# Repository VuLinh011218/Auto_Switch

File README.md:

# Auto Switch – Hệ thống giám sát và điều khiển thiết bị phòng

**STM32F103C8T6 | DHT22 · LDR · PIR | ILI9341 + XPT2046 | 4 relay**

[Thiết kế KiCad](Hardware/01_Design) · [Schematic PDF](Hardware/02_Schematic_PDF/Smart_Switch.pdf) · [BOM](Hardware/03_Bom) · [Gerber](Hardware/04_Gerber) · [Firmware – branch ILI9341](https://github.com/VuLinh011218/Auto_Switch/tree/ILI9341/Firmware)

## 1. Giới thiệu

Auto Switch là mạch giám sát các điều kiện trong phòng và điều khiển **quạt, hai đèn và máy hút ẩm**. STM32F103C8T6 đọc dữ liệu từ cảm biến nhiệt độ – độ ẩm, ánh sáng và chuyển động; trạng thái hệ thống được đưa lên màn hình TFT 2.8 inch. Người dùng thao tác bằng cảm ứng hoặc nút nhấn vật lý.

Hệ thống được thiết kế với hai chế độ:

- **Manual:** Người dùng bật/tắt từng thiết bị.
- **Auto:** Vi điều khiển điều khiển thiết bị theo dữ liệu cảm biến và ngưỡng đã đặt.

## 2. Chức năng

| Chức năng | Mô tả theo thiết kế |
| --- | --- |
| Đo môi trường | DHT22 đo nhiệt độ, độ ẩm; LDR đo mức sáng; PIR AM312 phát hiện chuyển động |
| Hiển thị | TFT ILI9341 hiển thị thông số môi trường, chế độ và trạng thái bốn thiết bị |
| Điều khiển bằng tay | Bật/tắt tải bằng màn hình cảm ứng XPT2046 hoặc nút nhấn |
| Điều khiển tự động | Quạt theo nhiệt độ, máy hút ẩm theo độ ẩm, hai đèn theo ánh sáng và chuyển động |
| Đầu ra | Bốn relay điều khiển quạt, đèn 1, đèn 2 và máy hút ẩm |

### Auto Mode

- **Quạt và máy hút ẩm:** đóng/ngắt theo các ngưỡng nhiệt độ, độ ẩm tương ứng.
- **Đèn 1 và đèn 2:** kết hợp tín hiệu PIR với hai ngưỡng ánh sáng riêng biệt. Khi trời tối hơn, đèn 2 được bật thêm; khi sáng trở lại, đèn 2 tắt trước đèn 1.
- **Thời gian giữ đèn:** mỗi lần PIR phát hiện chuyển động, bộ đếm 5 phút bắt đầu lại. Nếu không có chuyển động mới, hai đèn tắt khi hết thời gian.

## 3. Sơ đồ hệ thống

**Hình 1. Sơ đồ khối chức năng**

```mermaid
flowchart LR
    S["DHT22 / LDR / PIR"] --> MCU["STM32F103C8T6"]
    B["4 nút nhấn"] --> MCU
    T["XPT2046 Touch"] <-->|SPI2| MCU
    MCU -->|SPI1| LCD["TFT ILI9341"]
    MCU -->|GPIO| D["PC817 + transistor"]
    D --> R["4 relay 12 VDC"]
    R --> L["Quạt / Đèn 1 / Đèn 2 / Máy hút ẩm"]
```

**Figure 2. Power Distribution**

```mermaid
flowchart LR
    IN["12 V DC Adapter"] --> F["Fuse / Input Protection"]
    F --> V12["12 V Rail"]
    V12 --> RELAY["Four 12 V Relay Coils"]
    V12 --> BUCK["TPS54231 Buck Converter"]
    BUCK --> V33["3.3 V Rail"]
    V33 --> MCU["STM32F103C8T6"]
    V33 --> LCD["ILI9341 Display + XPT2046 Touch"]
    V33 --> SENS["DHT22 / LDR / PIR Sensors"]
```

## 4. Phần cứng

| Thành phần | Chức năng |
| --- | --- |
| STM32F103C8T6 | Vi điều khiển ARM Cortex-M3, xử lý cảm biến và lệnh điều khiển |
| DHT22 (AM2302) | Đo nhiệt độ và độ ẩm |
| LDR + LM393 | Đọc mức ánh sáng qua ngõ ra analog AO |
| PIR AM312 | Phát hiện chuyển động |
| ILI9341 2.8 inch | Màn hình TFT 240 × 320, giao tiếp SPI |
| XPT2046 | Bộ điều khiển cảm ứng, giao tiếp SPI |
| HF46F 12-HS1 (4 chiếc) | Relay điều khiển bốn tải |
| PC817 + transistor | Tầng điều khiển relay |
| TPS54231DR | Hạ áp 12 V xuống 3.3 V |
| 4 nút nhấn | Điều khiển trực tiếp tại thiết bị |

## 5. Firmware

(https://github.com/VuLinh011218/Auto_Switch/tree/ILI9341/Firmware).

```text
Firmware/
├── app/                 # Chọn chế độ, xử lý lệnh và ngưỡng điều khiển
├── middleware/
│   ├── input_mgr/       # Xử lý nút nhấn và cảm ứng
│   └── ui/              # Giao diện TFT
├── device/
│   ├── button/          # Nút nhấn, debounce
│   ├── ili9341/         # Driver màn hình
│   ├── relay/           # Điều khiển 4 relay
│   ├── sensor/          # Giao diện đọc cảm biến
│   └── xpt2046/         # Driver cảm ứng
├── Core/                # Khởi tạo MCU và ngoại vi
├── Drivers/             # STM32 HAL / CMSIS
└── Smart_Room_Control.ioc
```

## 6. Cấu trúc repository

```text
Auto_Switch/
├── Hardware/
│   ├── 01_Design/            # Project KiCad 10, schematic và PCB
│   ├── 02_Schematic_PDF/     # Bản PDF sơ đồ nguyên lý
│   ├── 03_Bom/               # Danh sách linh kiện
│   └── 04_Gerber/            # Gerber và drill files
├── Firmware/                 # Mã nguồn nằm trên branch ILI9341
└── .gitignore
```

## 7. Tài liệu dự án

- [Sơ đồ nguyên lý (PDF)](Hardware/02_Schematic_PDF/Smart_Switch.pdf)
- [Project KiCad](Hardware/01_Design/Smart_Switch.kicad_pro)
- [Thiết kế PCB](Hardware/01_Design/Smart_Switch.kicad_pcb)
- [Danh sách linh kiện (BOM)](Hardware/03_Bom/Smart_Switch.csv)
- [File Gerber](Hardware/04_Gerber)

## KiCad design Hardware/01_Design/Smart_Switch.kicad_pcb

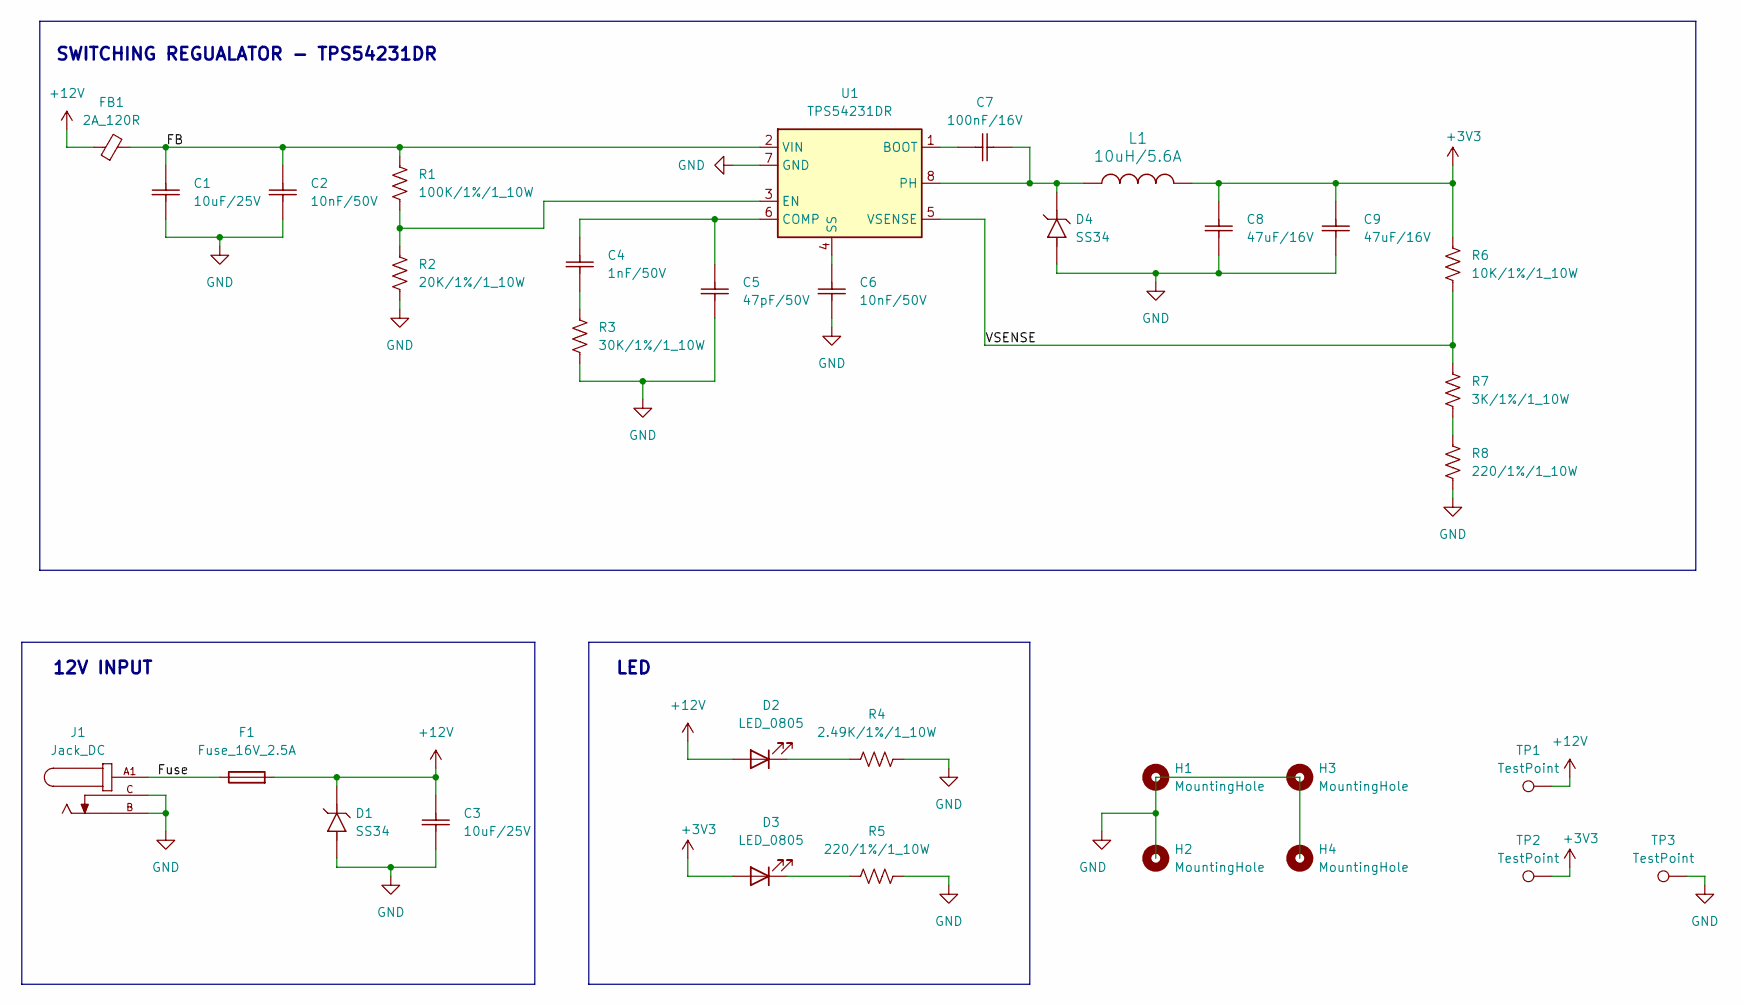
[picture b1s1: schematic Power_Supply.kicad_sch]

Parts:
C1, C3: 10uF/25V; Ceramic_Cap_0603
C2, C6: 10nF/50V; Ceramic_Cap_0603
C4: 1nF/50V; Ceramic_Cap_0603
C5: 47pF/50V; Ceramic_Cap_0603
C7: 100nF/16V; Ceramic_Cap_0603
C8, C9: 47uF/16V; Ceramic_Cap_1206
D1, D4: SS34; D_SMA
D2, D3: LED_0805
F1: Fuse_16V_2.5A; Fuse_1812_4532Metric
FB1: 2A_120R; FB_0805
H1, H2, H3, H4: MountingHole; MountingHole_3.2mm_M3_DIN965_Pad_TopBottom
J1: Jack_DC; Jack-DC
L1: 10uH/5.6A; IND_CD75NP_SUM
R1: 100K/1%/1_10W; Res_0603
R2: 20K/1%/1_10W; Res_0603
R3: 30K/1%/1_10W; Res_0603
R4: 2.49K/1%/1_10W; Res_0603
R5, R8: 220/1%/1_10W; Res_0603
R6: 10K/1%/1_10W; Res_0603
R7: 3K/1%/1_10W; Res_0603
TP1, TP2, TP3: TestPoint; TestPoint_Pad_2.0x2.0mm
U1: TPS54231DR; SOIC-8

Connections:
+3V3: C8.2, C9.2, D3.2 (A), L1.1, R6.2, TP2.1 (1_1); also elsewhere on the board
+12V: C3.2, D1.2 (K), D2.2 (A), F1.2, FB1.1, TP1.1 (1_1); also elsewhere on the board
/Power_Supply/FB: C1.2, C2.2, FB1.2, R1.2, U1.2 (VIN)
/Power_Supply/Fuse: F1.1, J1.A1, J1.A2
/Power_Supply/VSENSE: R6.1, R7.2, U1.5 (VSENSE)
GND: C1.1, C2.1, C3.1, C5.1, C6.1, C8.1, C9.1, D1.1 (A), D4.1 (A), J1.B, J1.C, R2.1, R3.1, R4.2, R5.2, R8.1, TP3.1 (1_1), U1.7 (GND); also elsewhere on the board
unnamed: C4.1, R3.2
unnamed: D2.1 (K), R4.1
unnamed: D3.1 (K), R5.1
unnamed: C7.1, D4.2 (K), L1.2, U1.8 (PH)
unnamed: R7.1, R8.2
unnamed: C7.2, U1.1 (BOOT)
unnamed: C4.2, C5.2, U1.6 (COMP)
unnamed: R1.1, R2.2, U1.3 (EN)
unnamed: C6.2, U1.4 (SS)

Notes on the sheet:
LED
SWITCHING REGUALATOR - TPS54231DR
12V INPUT

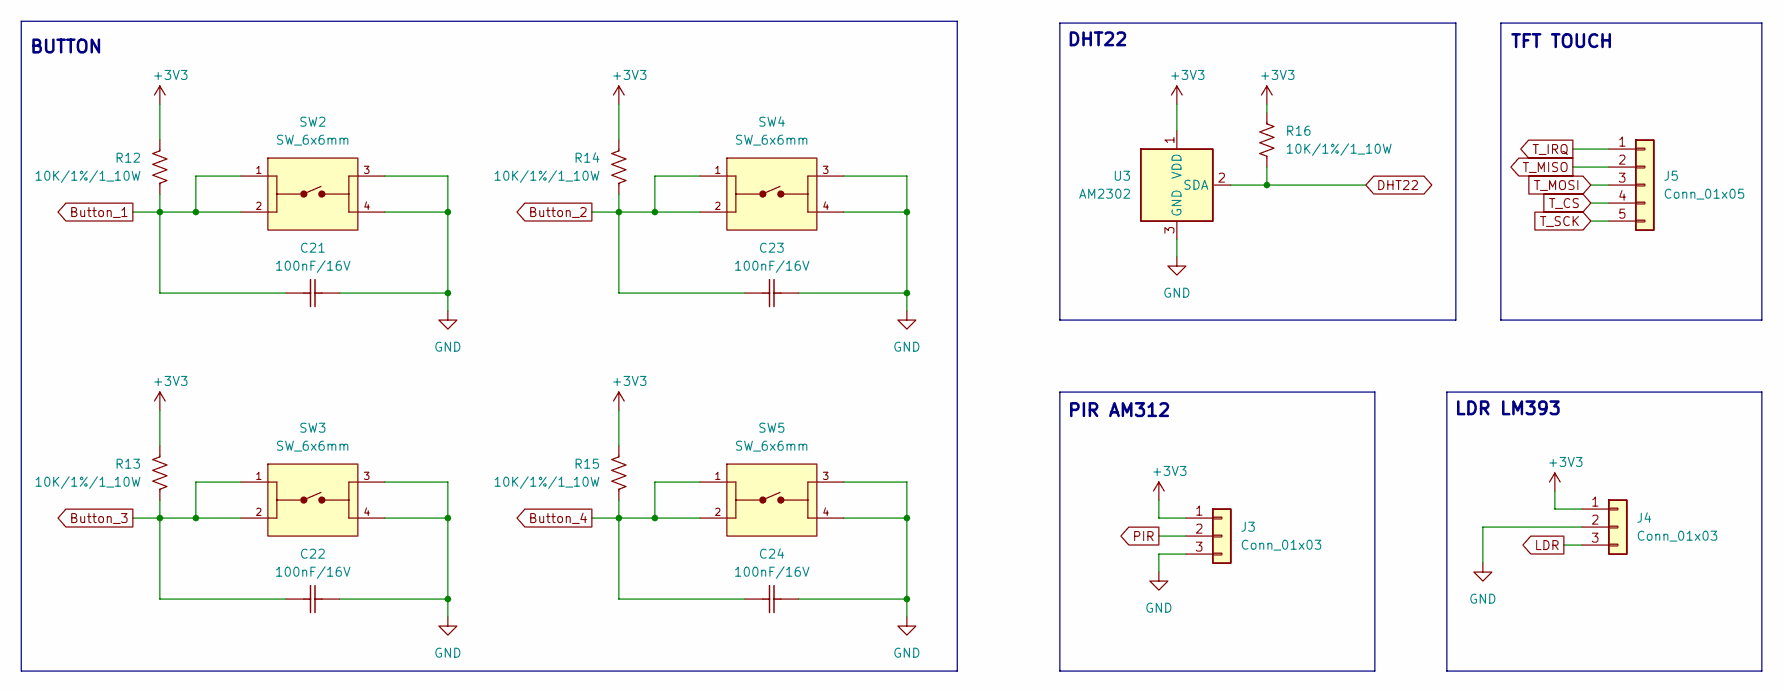
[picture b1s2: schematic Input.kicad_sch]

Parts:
C21, C22, C23, C24: 100nF/16V; Ceramic_Cap_0603
J3, J4: Conn_01x03; PinHeader_1x03_P2.54mm_Vertical
J5: Conn_01x05; PinHeader_1x05_P2.54mm_Vertical
R12, R13, R14, R15, R16: 10K/1%/1_10W; Res_0603
SW2, SW3, SW4, SW5: SW_6x6mm; TE_FSM4JSMA
U3: AM2302; ASAIR_AM2302_P2.54mm_Vertical

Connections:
+3V3: J3.1, J4.1, R12.1, R13.1, R14.1, R15.1, R16.2, U3.1 (VDD); also elsewhere on the board
Button_1: C21.1, R12.2, SW2.1, SW2.2; also elsewhere on the board
Button_2: C23.1, R14.2, SW4.1, SW4.2; also elsewhere on the board
Button_3: C22.1, R13.2, SW3.1, SW3.2; also elsewhere on the board
Button_4: C24.1, R15.2, SW5.1, SW5.2; also elsewhere on the board
DHT22: R16.1, U3.2 (SDA); also elsewhere on the board
GND: C21.2, C22.2, C23.2, C24.2, J3.3, J4.2, SW2.3, SW2.4, SW3.3, SW3.4, SW4.3, SW4.4, SW5.3, SW5.4, U3.3 (GND), U3.4 (GND); also elsewhere on the board
LDR: J4.3; also elsewhere on the board
PIR: J3.2; also elsewhere on the board
T_CS: J5.4; also elsewhere on the board
T_IRQ: J5.1; also elsewhere on the board
T_MISO: J5.2; also elsewhere on the board
T_MOSI: J5.3; also elsewhere on the board
T_SCK: J5.5; also elsewhere on the board

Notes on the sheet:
LDR LM393
BUTTON
TFT TOUCH
DHT22
PIR AM312

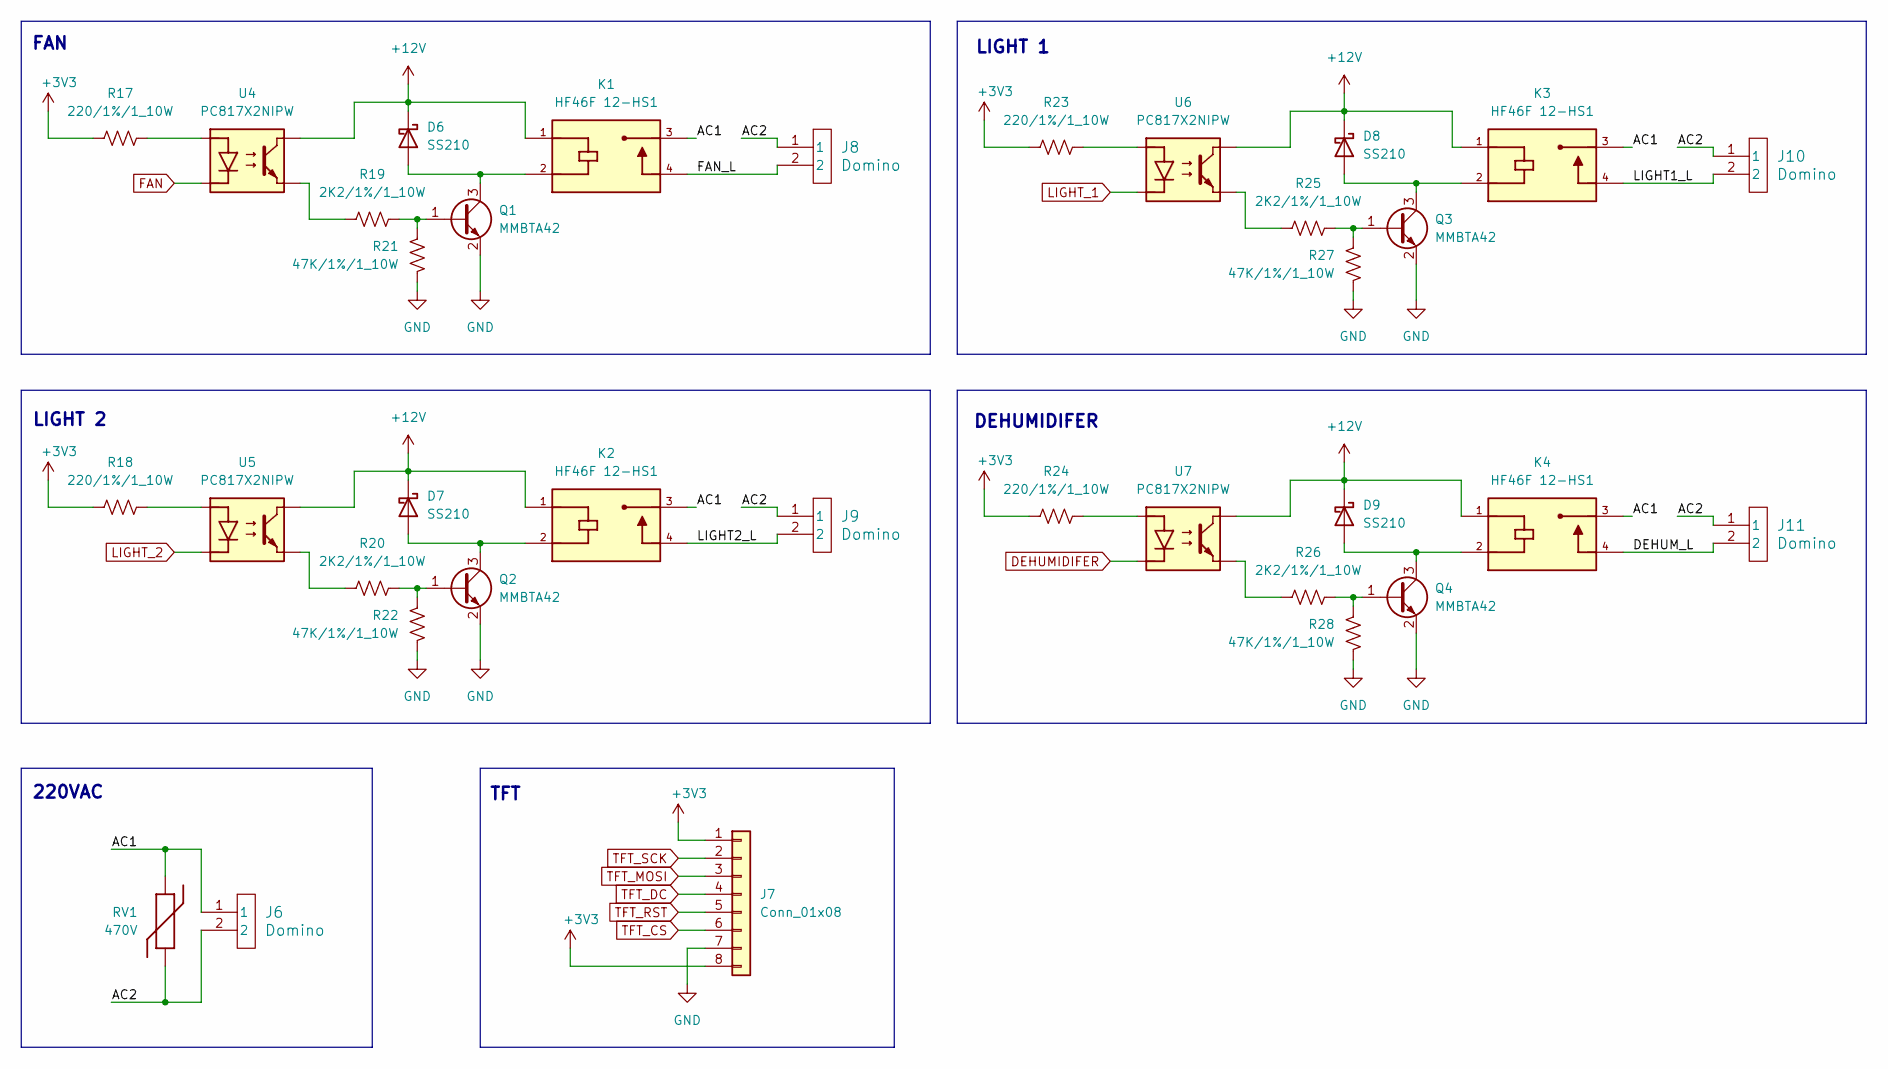
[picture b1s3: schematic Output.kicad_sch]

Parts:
D6, D7, D8, D9: SS210; D_SMA
J6, J8, J9, J10, J11: Domino; Domino_2P
J7: Conn_01x08; PinHeader_1x08_P2.54mm_Vertical
K1, K2, K3, K4: HF46F 12-HS1; RELAY_HF46F_005-HS1
Q1, Q2, Q3, Q4: MMBTA42; SOT-23
R17, R18, R23, R24: 220/1%/1_10W; Res_0603
R19, R20, R25, R26: 2K2/1%/1_10W; Res_0603
R21, R22, R27, R28: 47K/1%/1_10W; Res_0603
RV1: 470V; RV_Disc_D7mm_W3.4mm_P5mm
U4, U5, U6, U7: PC817X2NIPW

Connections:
+3V3: J7.1, J7.8, R17.1, R18.1, R23.1, R24.1; also elsewhere on the board
+12V: D6.1 (K), D7.1 (K), D8.1 (K), D9.1 (K), K1.1, K2.1, K3.1, K4.1, U4.4 (C), U5.4 (C), U6.4 (C), U7.4 (C); also elsewhere on the board
/Output/AC1: J6.1, K1.3, K2.3, K3.3, K4.3, RV1.2
/Output/AC2: J6.2, J8.1, J9.1, J10.1, J11.1, RV1.1
/Output/DEHUM_L: J11.2, K4.4
/Output/FAN_L: J8.2, K1.4
/Output/LIGHT1_L: J10.2, K3.4
/Output/LIGHT2_L: J9.2, K2.4
DEHUMIDIFER: U7.2 (K); also elsewhere on the board
FAN: U4.2 (K); also elsewhere on the board
GND: J7.7, Q1.2 (E), Q2.2 (E), Q3.2 (E), Q4.2 (E), R21.1, R22.1, R27.1, R28.1; also elsewhere on the board
LIGHT_1: U6.2 (K); also elsewhere on the board
LIGHT_2: U5.2 (K); also elsewhere on the board
unnamed: D6.2 (A), K1.2, Q1.3 (C)
unnamed: D7.2 (A), K2.2, Q2.3 (C)
unnamed: D8.2 (A), K3.2, Q3.3 (C)
unnamed: D9.2 (A), K4.2, Q4.3 (C)
unnamed: Q1.1 (B), R19.2, R21.2
unnamed: Q2.1 (B), R20.2, R22.2
unnamed: Q3.1 (B), R25.2, R27.2
unnamed: Q4.1 (B), R26.2, R28.2
unnamed: R17.2, U4.1 (A)
unnamed: R19.1, U4.3 (E)
unnamed: R18.2, U5.1 (A)
unnamed: R20.1, U5.3 (E)
unnamed: R23.2, U6.1 (A)
unnamed: R25.1, U6.3 (E)
unnamed: R24.2, U7.1 (A)
unnamed: R26.1, U7.3 (E)
TFT_CS: J7.6; also elsewhere on the board
TFT_DC: J7.4; also elsewhere on the board
TFT_MOSI: J7.3; also elsewhere on the board
TFT_RST: J7.5; also elsewhere on the board
TFT_SCK: J7.2; also elsewhere on the board

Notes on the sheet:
LIGHT 2
220VAC
LIGHT 1
FAN
TFT
DEHUMIDIFER

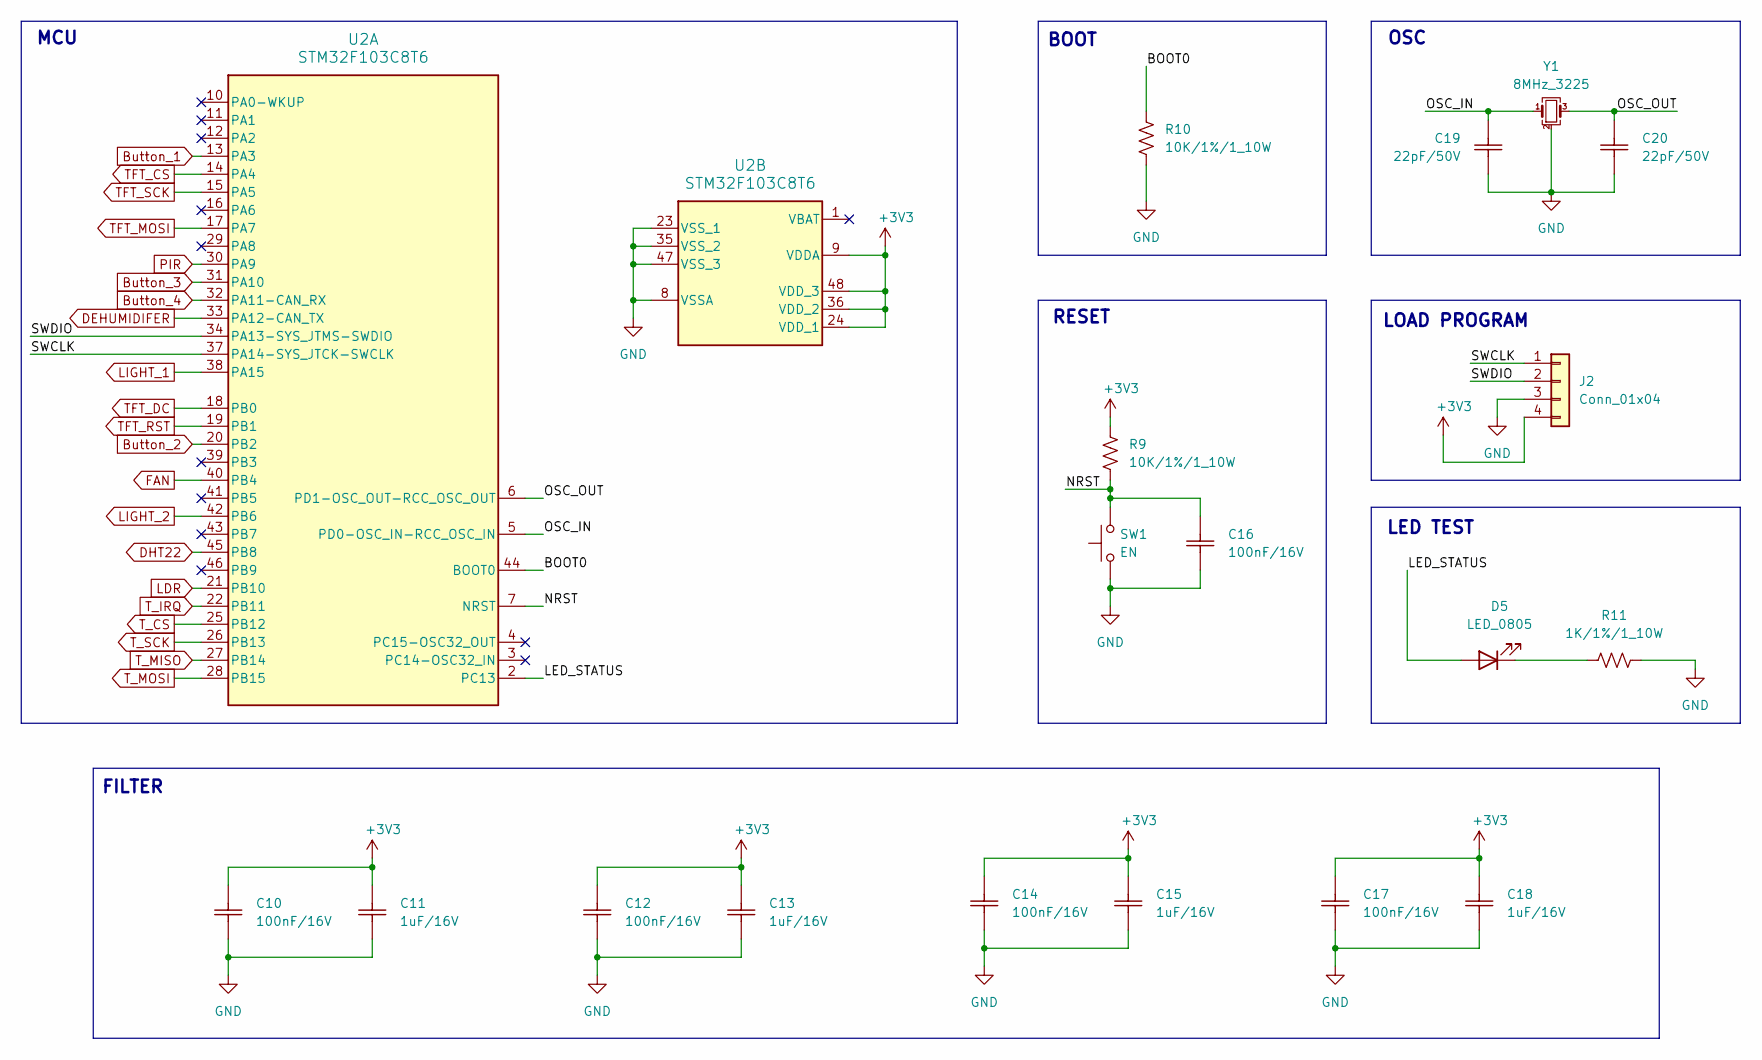
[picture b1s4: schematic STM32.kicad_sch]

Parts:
C10, C12, C14, C16, C17: 100nF/16V; Ceramic_Cap_0603
C11, C13, C15, C18: 1uF/16V; Ceramic_Cap_0603
C19, C20: 22pF/50V; Ceramic_Cap_0603
D5: LED_0805
J2: Conn_01x04; PinHeader_1x04_P2.54mm_Vertical
R9, R10: 10K/1%/1_10W; Res_0603
R11: 1K/1%/1_10W; Res_0603
SW1: EN; SW_SMD
U2: STM32F103C8T6; QFP50P900X900X160-48N
Y1: 8MHz_3225; Crystal_SMD_4PIN_3225

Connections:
+3V3: C10.2, C11.2, C12.2, C13.2, C14.2, C15.2, C17.2, C18.2, J2.4, R9.2, U2.9 (VDDA), U2.24 (VDD_1), U2.36 (VDD_2), U2.48 (VDD_3); also elsewhere on the board
/STM32/BOOT0: R10.2, U2.44 (BOOT0)
/STM32/LED_STATUS: D5.2 (A), U2.2 (PC13)
/STM32/NRST: C16.2, R9.1, SW1.2, U2.7 (NRST)
/STM32/OSC_IN: C19.2, U2.5 (PD0-OSC_IN-RCC_OSC_IN), Y1.1
/STM32/OSC_OUT: C20.2, U2.6 (PD1-OSC_OUT-RCC_OSC_OUT), Y1.3
/STM32/SWCLK: J2.1, U2.37 (PA14-SYS_JTCK-SWCLK)
/STM32/SWDIO: J2.2, U2.34 (PA13-SYS_JTMS-SWDIO)
Button_1: U2.13 (PA3); also elsewhere on the board
Button_2: U2.20 (PB2); also elsewhere on the board
Button_3: U2.31 (PA10); also elsewhere on the board
Button_4: U2.32 (PA11-CAN_RX); also elsewhere on the board
DEHUMIDIFER: U2.33 (PA12-CAN_TX); also elsewhere on the board
DHT22: U2.45 (PB8); also elsewhere on the board
FAN: U2.40 (PB4); also elsewhere on the board
GND: C10.1, C11.1, C12.1, C13.1, C14.1, C15.1, C16.1, C17.1, C18.1, C19.1, C20.1, J2.3, R10.1, R11.1, SW1.1, U2.8 (VSSA), U2.23 (VSS_1), U2.35 (VSS_2), U2.47 (VSS_3), Y1.2 (G), Y1.4 (G); also elsewhere on the board
LDR: U2.21 (PB10); also elsewhere on the board
LIGHT_1: U2.38 (PA15); also elsewhere on the board
LIGHT_2: U2.42 (PB6); also elsewhere on the board
unnamed: D5.1 (K), R11.2
PIR: U2.30 (PA9); also elsewhere on the board
TFT_CS: U2.14 (PA4); also elsewhere on the board
TFT_DC: U2.18 (PB0); also elsewhere on the board
TFT_MOSI: U2.17 (PA7); also elsewhere on the board
TFT_RST: U2.19 (PB1); also elsewhere on the board
TFT_SCK: U2.15 (PA5); also elsewhere on the board
T_CS: U2.25 (PB12); also elsewhere on the board
T_IRQ: U2.22 (PB11); also elsewhere on the board
T_MISO: U2.27 (PB14); also elsewhere on the board
T_MOSI: U2.28 (PB15); also elsewhere on the board
T_SCK: U2.26 (PB13); also elsewhere on the board

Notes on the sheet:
MCU
RESET
BOOT
OSC
FILTER
LOAD PROGRAM
LED TEST

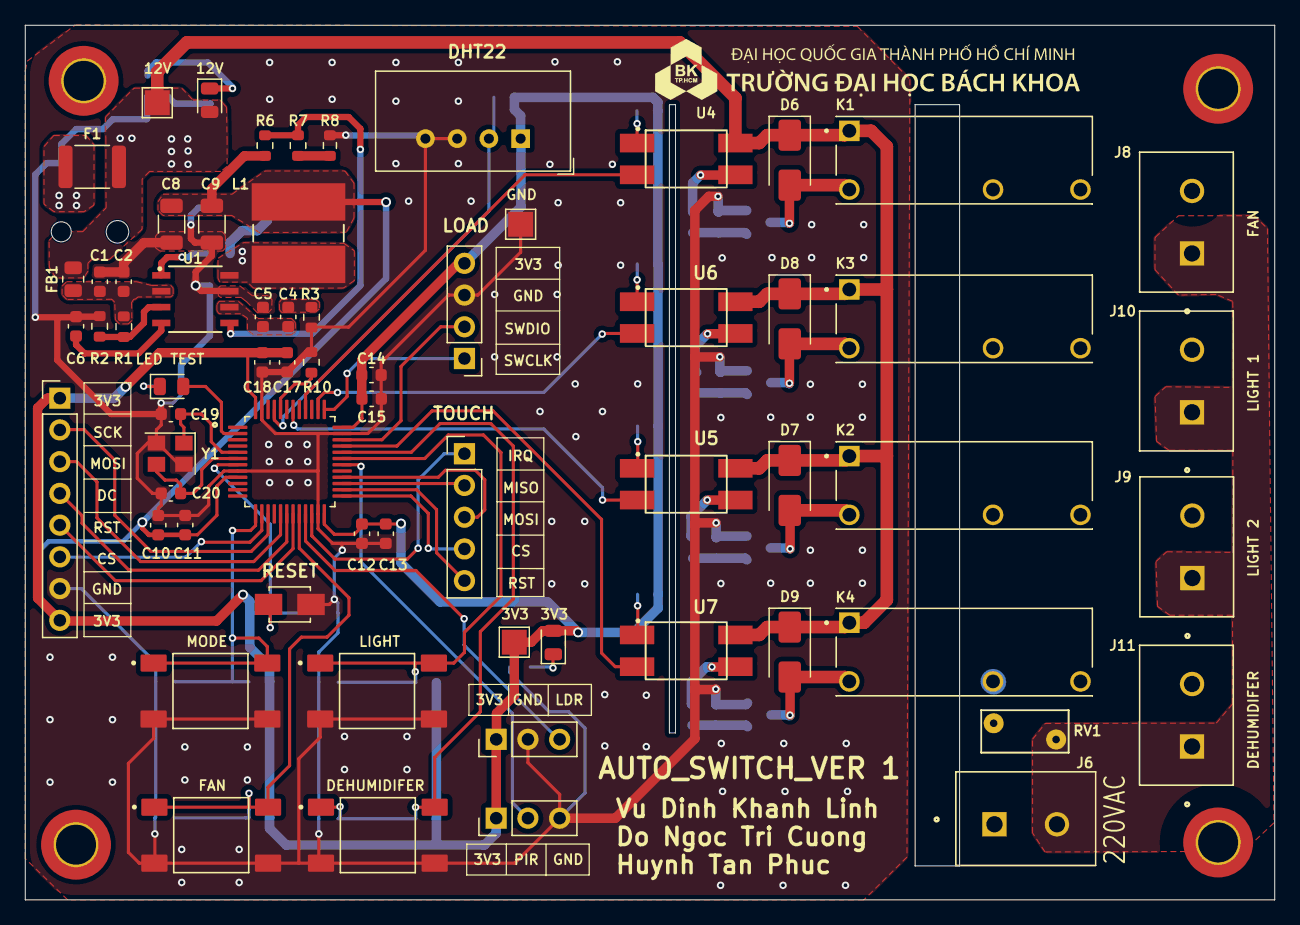
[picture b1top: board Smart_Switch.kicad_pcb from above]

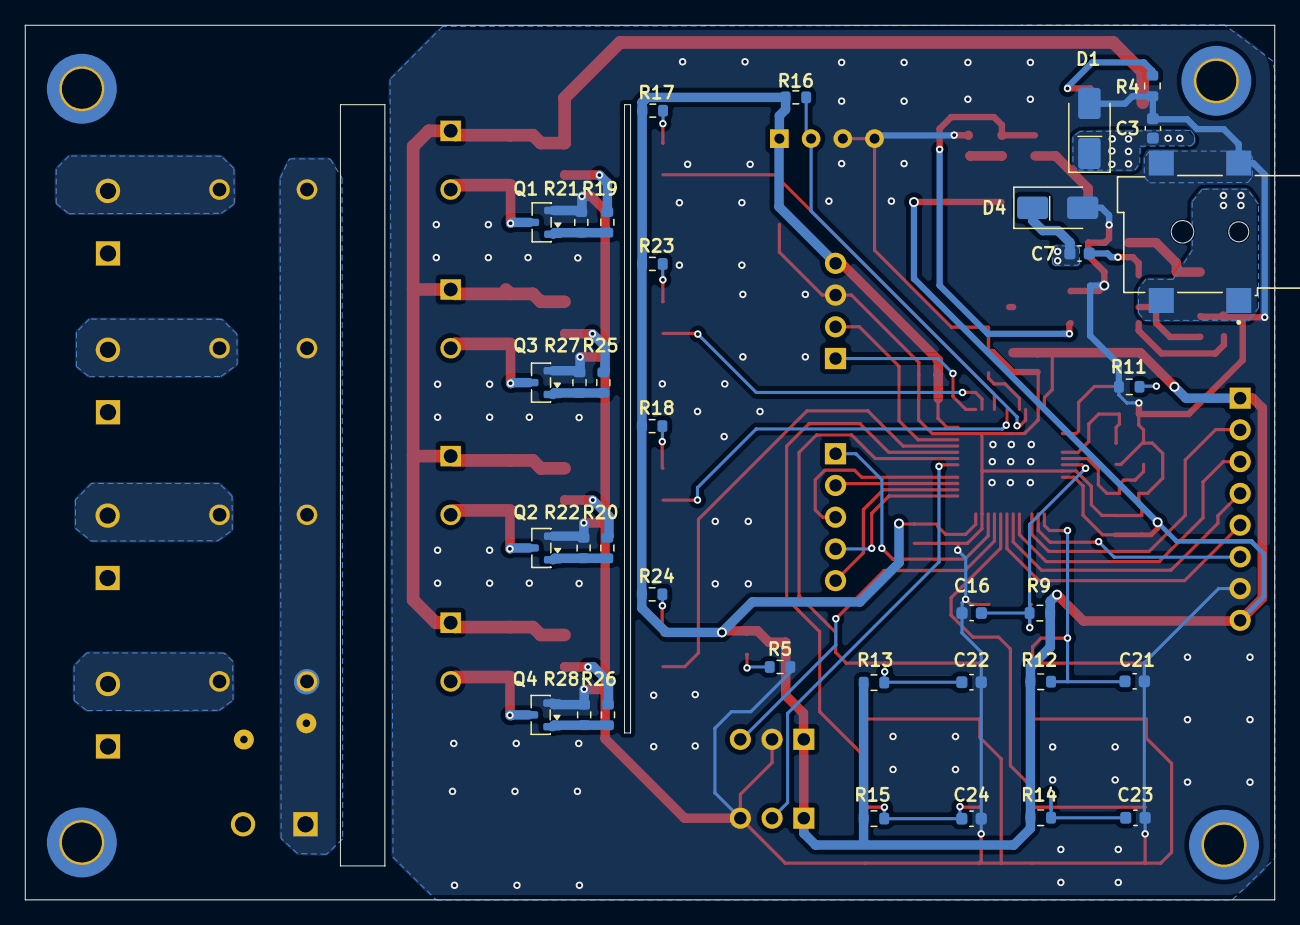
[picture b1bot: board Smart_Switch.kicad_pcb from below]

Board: 2 copper layers, 100.0 x 70.0 mm, 104 parts (35 on the bottom side), 66 nets.

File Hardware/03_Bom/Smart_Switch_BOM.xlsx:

Reference | Qty | Value | Supply part number | Supply name | Supply URL
C1,C3 | 2 | 10uF/25V | Tụ Gốm 0603 10uF 25V | Thegioiic | https://www.thegioiic.com/tu-gom-0603-10uf-25v
C2,C6 | 2 | 10nF/50V | Tụ Gốm 0603 10nF 50V | Thegioiic | https://www.thegioiic.com/tu-gom-0603-10nf-50v
C4 | 1 | 1nF/50V | Tụ Gốm 0603 1nF 50V | Thegioiic | https://www.thegioiic.com/tu-gom-0603-1nf-50v
C5 | 1 | 47pF/50V | Tụ Gốm 0603 47pF 50V | Thegioiic | https://www.thegioiic.com/tu-gom-0603-47pf-50v
C7,C10,C12,C14,C16,C17,C21,C22,C23,C24 | 10 | 100nF/16V | Tụ Gốm 0603 100nF (0.1uF) 16V | Thegioiic | https://www.thegioiic.com/tu-gom-0603-100nf-0-1uf-16v
C8,C9 | 2 | 47uF/16V | Tụ Gốm 1206 47uF 16V | Thegioiic | https://www.thegioiic.com/tu-gom-1206-47uf-16v
C11,C13,C15,C18 | 4 | 1uF/16V | Tụ Gốm 0603 1uF 16V | Thegioiic | https://www.thegioiic.com/tu-gom-0603-1uf-16v
C19,C20 | 2 | 22pF/50V | Tụ Gốm 0603 22pF 50V | Thegioiic | https://www.thegioiic.com/tu-gom-0603-22pf-50v
D1,D4 | 2 | SS34 | SS34 SMA Diode Shotky 3A 40V | Thegioiic | https://www.thegioiic.com/ss34-smc-diode-schottky-3a
D2,D3,D5 | 3 | LED_0805 | LED Xanh Lá 0805 Dán SMD Trong Suốt | Thegioiic | https://www.thegioiic.com/led-xanh-la-0805-dan-smd-trong-suot
D6,D7,D8,D9 | 4 | SS210 | SS210 SMA Diode Schottky 2A 100V | Thegioiic | https://www.thegioiic.com/ss210-sma-diode-schottky-2a-100v
F1 | 1 | Fuse_16V_2.5A | MF-MSMF250/16 Cầu Chì Tự Phục Hồi 1812 16V 2.5A | Thegioiic | https://www.thegioiic.com/mf-msmf250-16-cau-chi-tu-phuc-hoi-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
FB1 | 1 | 2A_120R | CBW201209U121T | Thegioiic | https://www.thegioiic.com/cbw201209u121t-ferrite-beads-2a-12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
J1 | 1 | Jack_DC | DC050 Đầu Nối Nguồn DC Cái 5521 Dán SMD Kim 2.1mm | Thegioiic | https://www.thegioiic.com/dc050-dau-noi-nguon-dc-cai-5521-da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
J2 | 1 | Conn_01x04 | Hàng Rào Đực Đơn 2.54mm 40 Chân 1 Hàng Cao 11.2mm Xuyên Lỗ Mạ Vàng | Thegioiic | https://www.thegioiic.com/hang-rao-duc-don-2-54mm-40-chan-1-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
J3,J4 | 2 | Conn_01x03 | Hàng Rào Cái Đơn 2.54mm 3 Chân 1 Hàng Cao 11.8mm Xuyên Lỗ | Thegioiic | https://www.thegioiic.com/hang-rao-cai-don-2-54mm-3-chan-1-h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
J5 | 1 | Conn_01x05 | Hàng Rào Cái Đơn 2.54mm 5 Chân 1 Hàng Cao 11.8mm Xuyên Lỗ | Thegioiic | https://www.thegioiic.com/hang-rao-cai-don-2-54mm-5-chan-1-h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
J6,J8,J9,J10,J11 | 5 | Domino | KF128-2-V Domino 2 Chân Thẳng 5mm 300V 10A Hàn PCB Loại Tốt | Thegioiic | https://www.thegioiic.com/kf128-2-v-domino-2-chan-thang-5mm-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
J7 | 1 | Conn_01x08 | Hàng Rào Cái Đơn 2.54mm 8 Chân 1 Hàng Cao 11.8mm Xuyên Lỗ | Thegioiic | https://www.thegioiic.com/hang-rao-cai-don-2-54mm-8-chan-1-h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
K1,K2,K3,K4 | 4 | HF46F 12-HS1 | HF46F 12-HS1 Rơ Le 12VDC 5A SPST-NO 4 Chân | Thegioiic | https://www.thegioiic.com/hf46f-12-hs1-ro-le-12vdc-5a-spst-n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
L1 | 1 | 10uH/5.6A | Cuộn Cảm Dán SMD CDRH104 1038-100 10uH 5.6A | Thegioiic | https://www.thegioiic.com/cuon-cam-dan-smd-cdrh104-1038-100-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
Q1,Q2,Q3,Q4 | 4 | MMBTA42 | MMBTA42 Transistor NPN 300V 0.5A 3 Chân SOT-23 | Thegioiic | https://www.thegioiic.com/mmbta42-transistor-npn-300v-0-5a-3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
R1 | 1 | 100K/1%/1_10W | Điện Trở 100 KOhm 0603 1% | Thegioiic | https://www.thegioiic.com/dien-tro-100-kohm-0603-1-
R2 | 1 | 20K/1%/1_10W | Điện Trở 20 KOhm 0603 1% | Thegioiic | https://www.thegioiic.com/dien-tro-20-kohm-0603-1-
R3 | 1 | 30K/1%/1_10W | Điện Trở 30 KOhm 0603 1% | Thegioiic | https://www.thegioiic.com/dien-tro-30-kohm-0603-1-
R4 | 1 | 2.49K/1%/1_10W | Điện Trở 2.49 KOhm 0603 1% | Thegioiic | https://www.thegioiic.com/dien-tro-2-49-kohm-0603-1-
R5,R8,R17,R18,R23,R24 | 6 | 220/1%/1_10W | Điện Trở 220 Ohm 0603 1% | Thegioiic | https://www.thegioiic.com/dien-tro-220-ohm-0603-1-
R6,R9,R10,R12,R13,R14,R15 | 7 | 10K/1%/1_10W | Điện Trở 10 KOhm 0603 1% | Thegioiic | https://www.thegioiic.com/dien-tro-10-kohm-0603-1-
R7 | 1 | 3K/1%/1_10W | Điện Trở 3 KOhm 0603 1% | Thegioiic | https://www.thegioiic.com/dien-tro-3-kohm-0603-1-
R11 | 1 | 1K/1%/1_10W | Điện Trở 1 KOhm 0603 1% | Thegioiic | https://www.thegioiic.com/dien-tro-1-kohm-0603-1-
R16 | 1 | 4.7/1%/1_10W | Điện Trở 4.7 Ohm 0603 1% | Thegioiic | https://www.thegioiic.com/dien-tro-4-7-ohm-0603-1-
R19,R20,R25,R26 | 4 | 2K2/1%/1_10W | Điện Trở 2.2 KOhm 0603 1% | Thegioiic | https://www.thegioiic.com/dien-tro-2-2-kohm-0603-1-
R21,R22,R27,R28 | 4 | 47K/1%/1_10W | Điện Trở 47 KOhm 0603 1% | Thegioiic | https://www.thegioiic.com/dien-tro-47-kohm-0603-1-
RV1 | 1 | 470V | Tụ Chống Sét Varistor 07D471K 470V | Thegioiic | https://www.thegioiic.com/tu-chong-set-varistor-07d471k-470v
SW1 | 1 | EN | Nút Nhấn 3x4mm Cao 2.5mm 2 Chân SMD | Thegioiic | https://www.thegioiic.com/nut-nhan-3x4mm-cao-2-5mm-2-chan-smd
SW2,SW3,SW4,SW5 | 4 | SW_6x6mm | Nút Nhấn 6x6mm Cao 4.3mm 4 Chân SMD | Thegioiic | https://www.thegioiic.com/nut-nhan-6x6mm-cao-4-3mm-4-chan-smd
TP1,TP2,TP3 | 3 | TestPoint
U1 | 1 | TPS54231DR | TPS54231DR IC Điều Chỉnh Giảm Áp 2A 8-SOIC | Thegioiic | https://www.thegioiic.com/tps54231dr-ic-dieu-chinh-giam-ap-2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
U2 | 1 | STM32F103C8T6 | STM32F103C8T6, 32-Bit ARM Cortex M3 Microcontroller, 72MHz, 64KB FLASH, 48-LQFP | Thegioiic | https://www.thegioiic.com/stm32f103c8t6-32-bit-arm-cortex-m3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
U3 | 1 | AM2302 | DHT22 AM2302 Cảm Biến Nhiệt Độ Độ Ẩm | Thegioiic | https://www.thegioiic.com/dht22-am2302-cam-bien-nhiet-do-do-am
U4,U5,U6,U7 | 4 | PC817X2NIPW | PC817X2NIPW Optoisolator Transistor Output 5000Vrms 1 Channel, SOP-4 | Thegioiic | https://www.thegioiic.com/pc817x2nipw-optoisolator-transisto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
Y1 | 1 | 8MHz_3225 | Thạch Anh 8MHz 3225 4 Chân SMD | Thegioiic | https://www.thegioiic.com/thach-anh-8mhz-3225-4-chan-smd

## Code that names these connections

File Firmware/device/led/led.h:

#ifndef LED_H
#define LED_H

#include <stdbool.h>
#include <stdint.h>

/* LED indices used by the whole firmware. Pin mapping: see Hardware/05_Report/report_sche.md */
typedef enum
{
    LED_STATUS = 0, /* PC13 - system status LED */
    LED_CH1,        /* PA11 - channel 1 indicator */
    LED_CH2,        /* PA12 - channel 2 indicator */
    LED_CH3,        /* PB9  - channel 3 indicator */
    LED_CH4,        /* PB10 - channel 4 indicator */
    LED_COUNT
} led_id_t;

/* Turn a LED on (true) or off (false). Polarity is handled inside led.c. */
void led_set(led_id_t led, bool state);

/* Invert the current state of a LED. Use this for blinking. */
void led_toggle(led_id_t led);

#endif /* LED_H */
